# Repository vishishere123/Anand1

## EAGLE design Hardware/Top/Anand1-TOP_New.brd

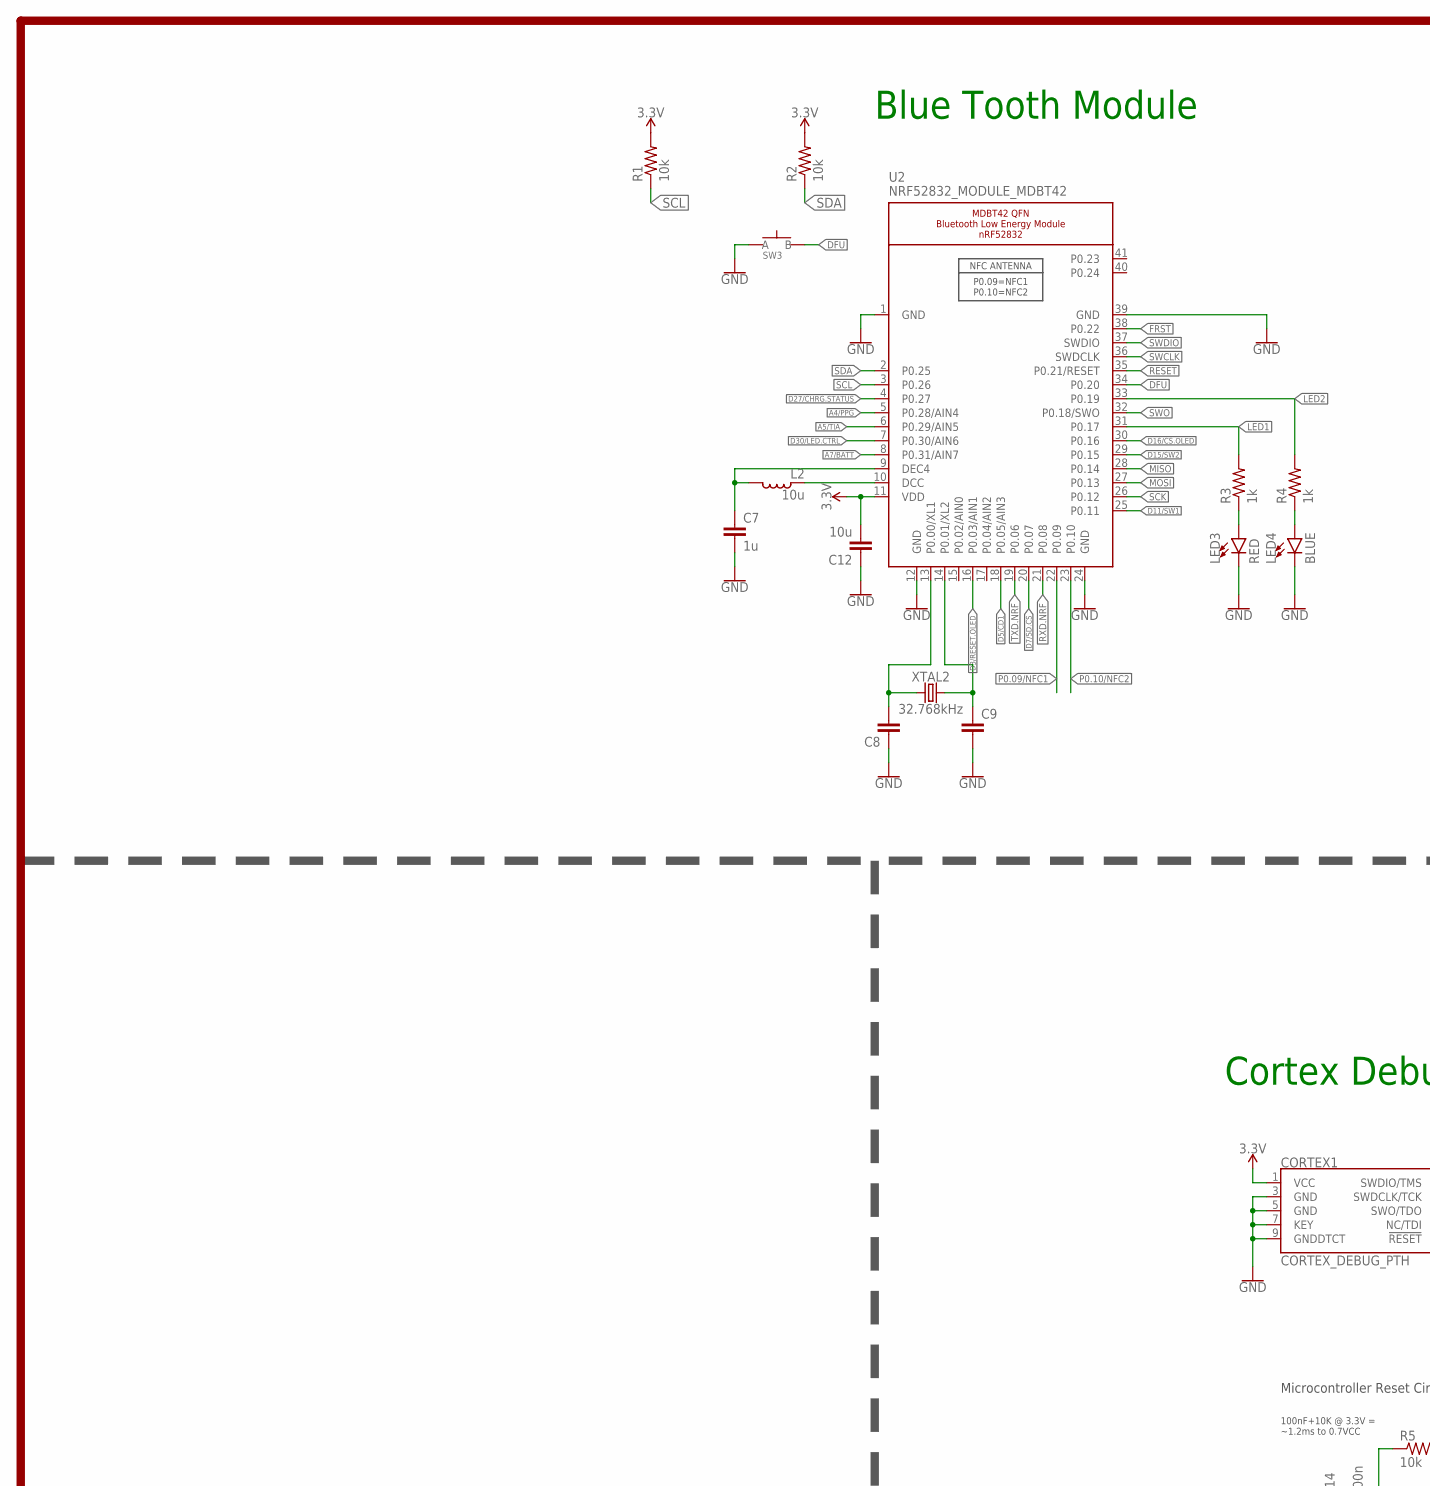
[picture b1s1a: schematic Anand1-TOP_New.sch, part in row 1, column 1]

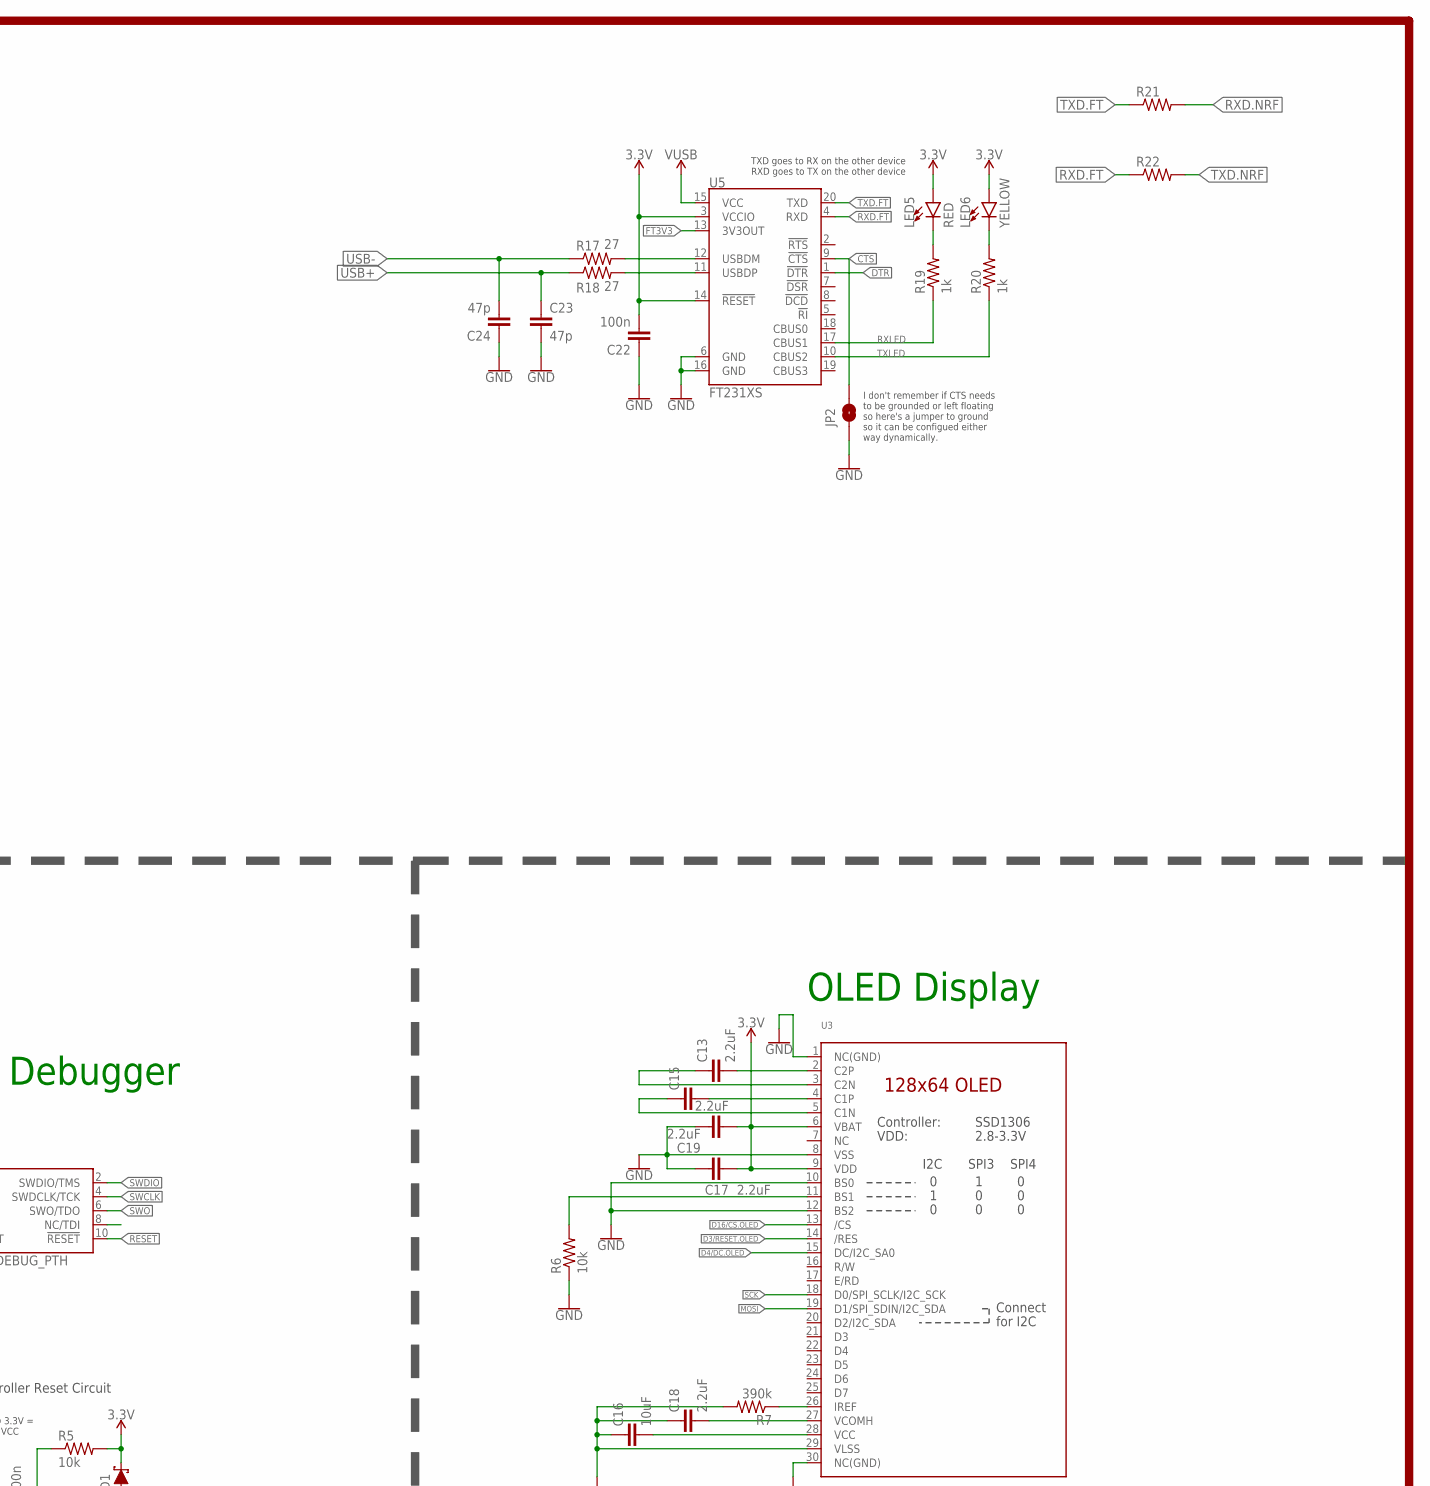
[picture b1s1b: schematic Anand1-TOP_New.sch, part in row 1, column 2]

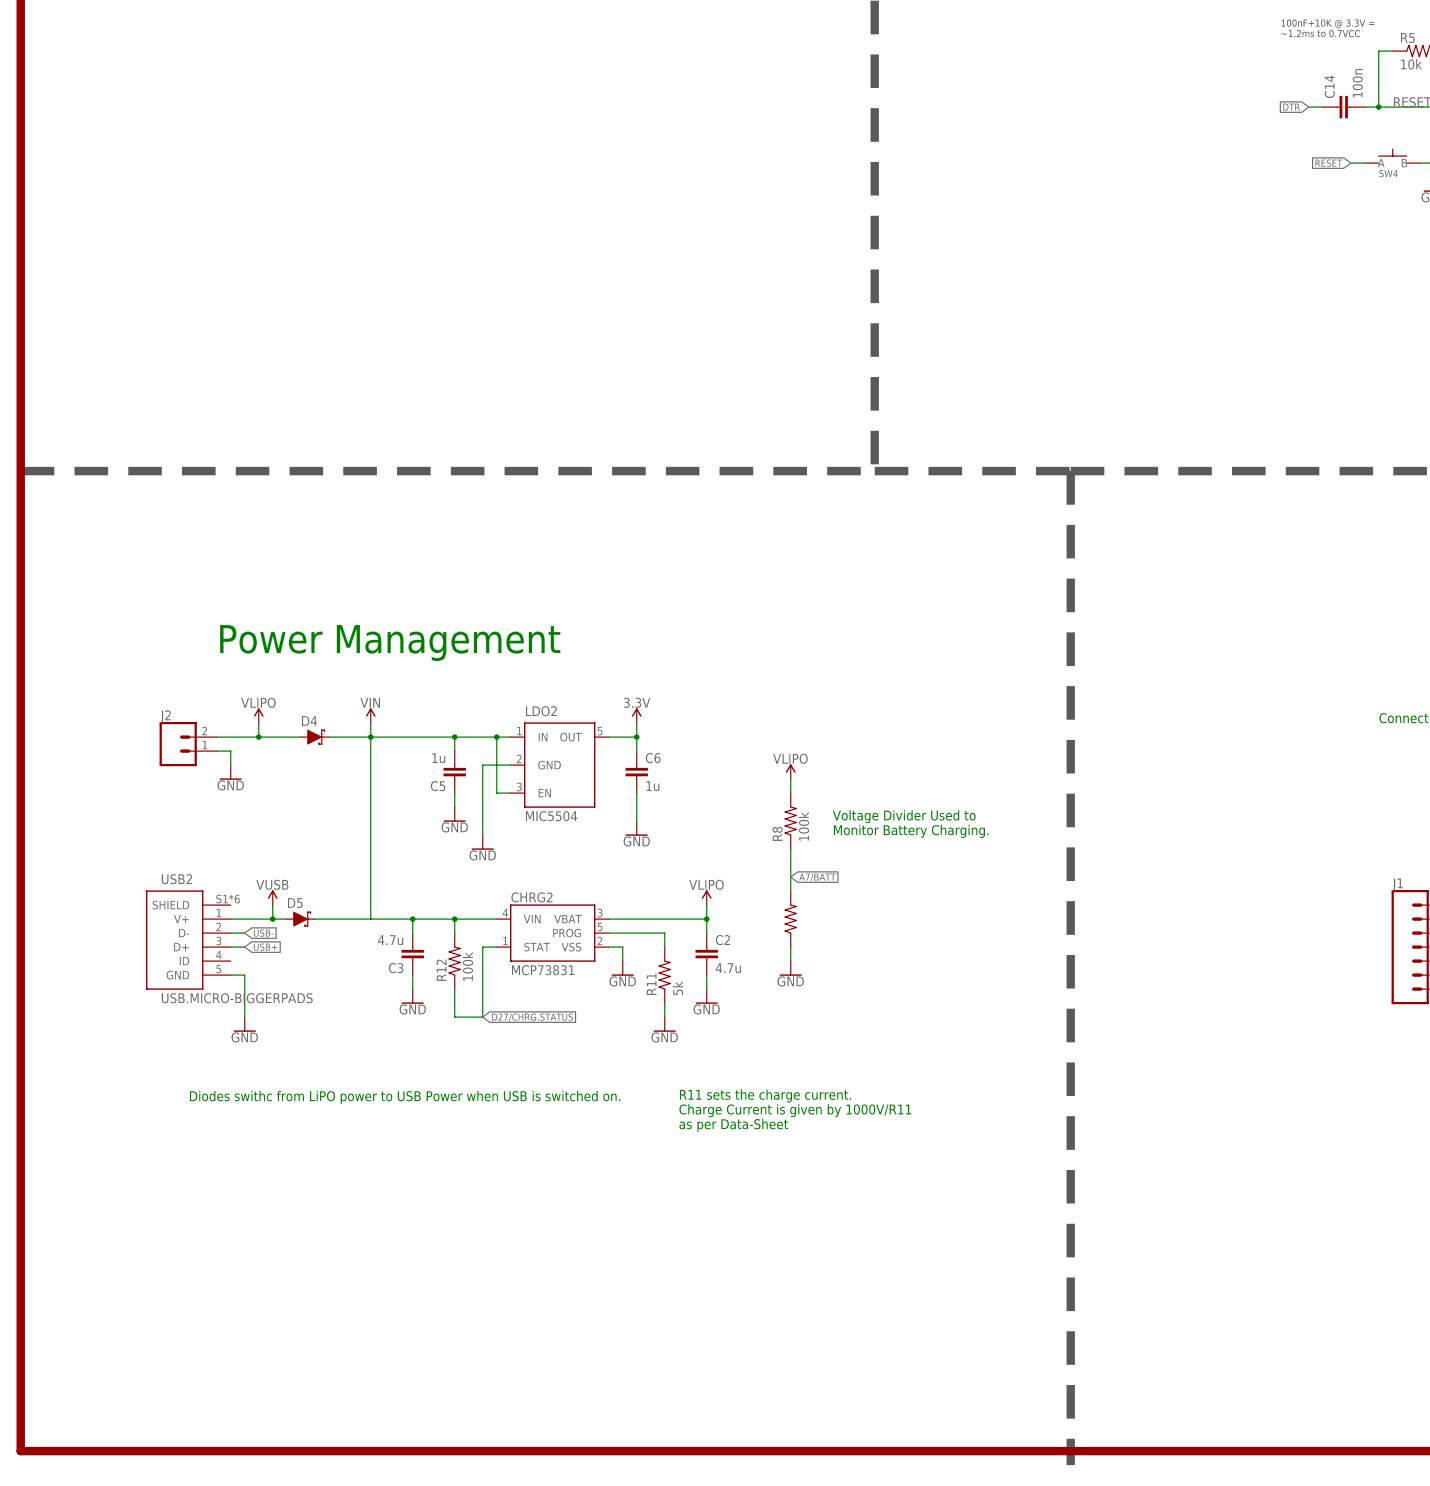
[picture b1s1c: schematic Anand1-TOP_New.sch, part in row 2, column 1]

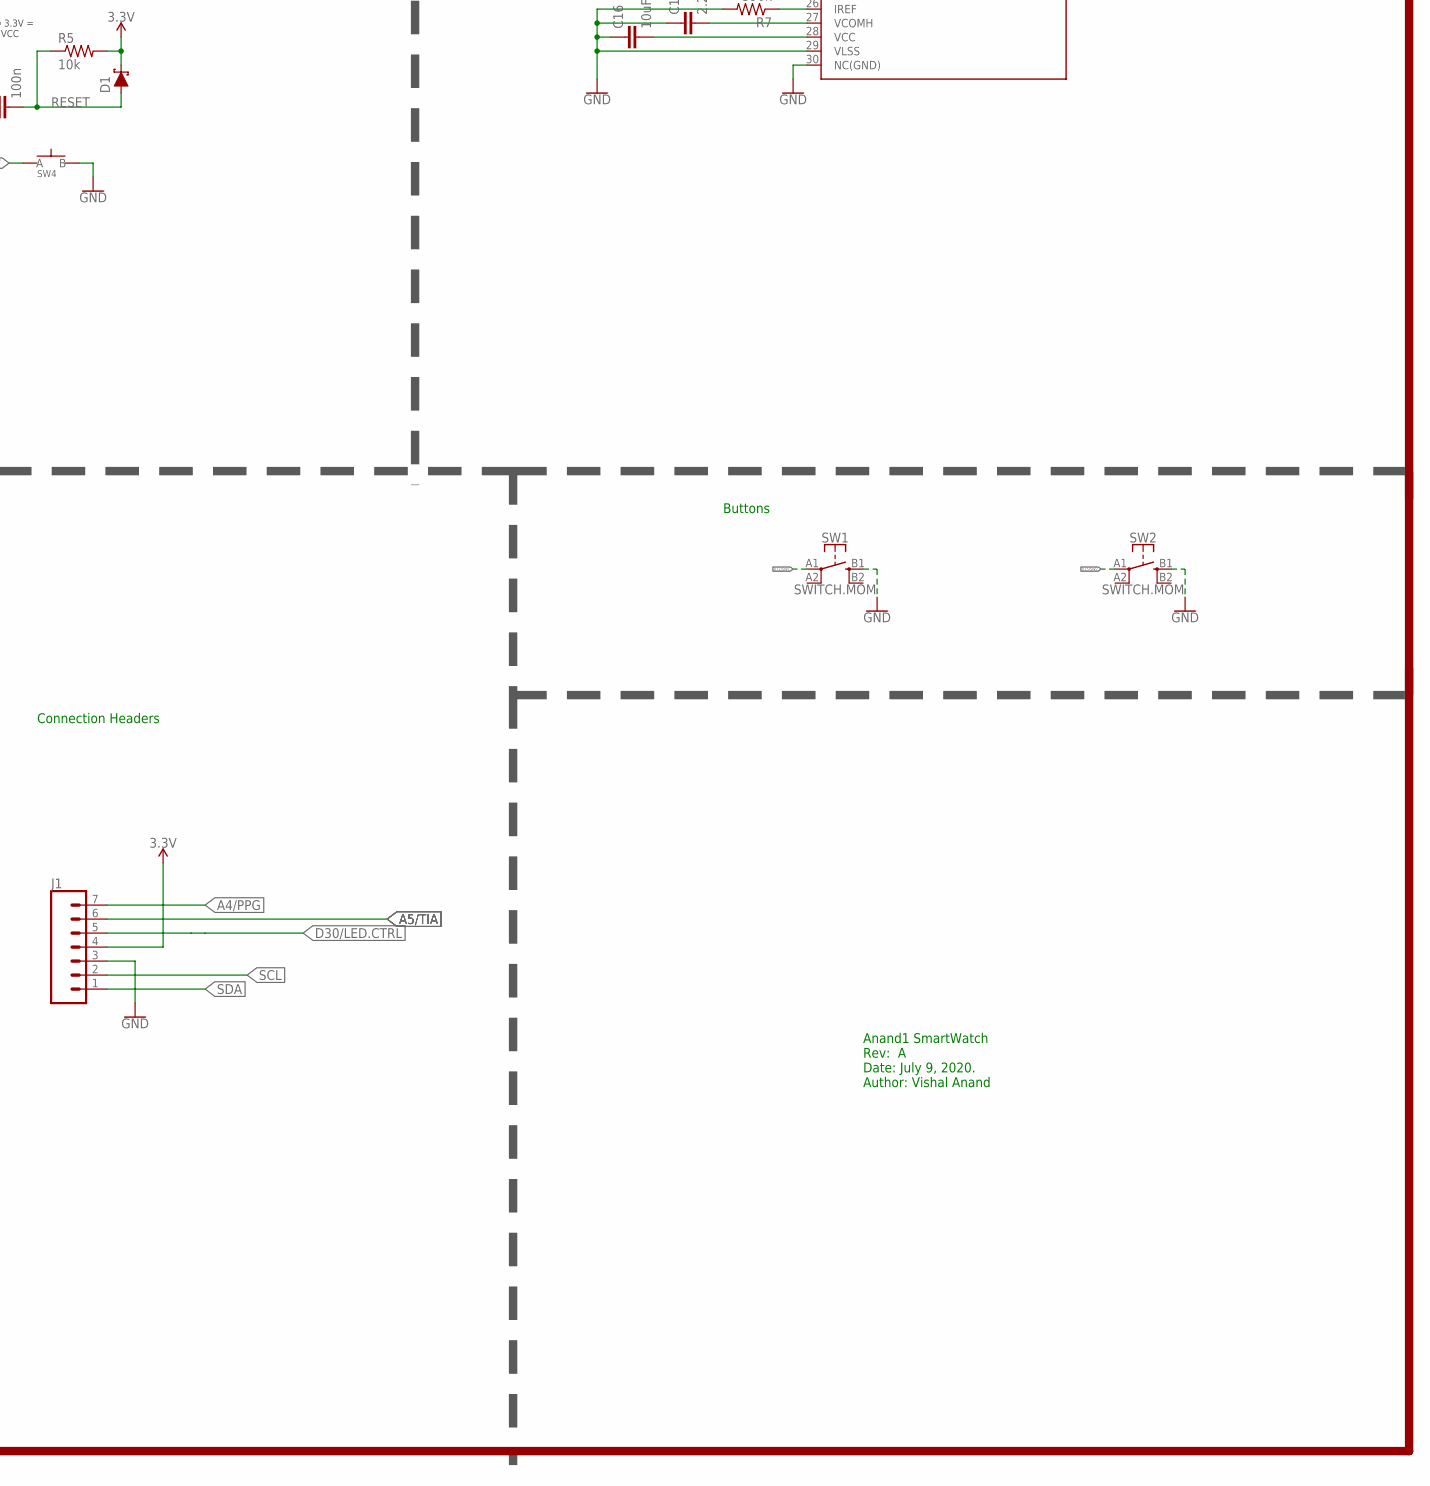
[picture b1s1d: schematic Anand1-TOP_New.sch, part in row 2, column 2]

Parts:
C2, C3: 4.7u; C0603
C5, C6, C7: 1u; C0603
C8, C9: CAPACITOR0603; C0603
C12: 10u; C0805
C13, C15, C17, C18, C19: 2.2uF; C0402
C14, C22: 100n; C0603
C16: 10uF; C0603
C23, C24: 47p; C0603
CHRG2: MCP73831; SOT23-5
CORTEX1: CORTEX_DEBUG_PTH; 2X5-PTH-1.27MM
D1, D4, D5: SCHOTTKY-USC; USC
J1: CONN_07-1.27MM; 1X07_1.27MM
J2: CONN_02; 1X02
JP2: JUMPER-SMT_2_NO_SILK; SMT-JUMPER_2_NO_SILK
L2: 10u; L0603
LDO2: MIC5504; SOT23-5
LED3, LED5: RED; LED-0603
LED4: BLUE; LED-0603
LED6: YELLOW; LED-0603
R1, R2, R5, R6: 10k; R0603
R3, R4, R19, R20: 1k; R0603
R7: 390k; R0603
R8, R9, R12: 100k; R0603
R11: 5k; R0603
R17, R18: 27; R0603
R21, R22: RESISTOR0603; R0603
SW1, SW2: SWITCH.MOM; TACTILE_SWITCH_SMD_6.2MM_TALL
SW3, SW4: SPST-PTS830GG140-COPY.1-3; BUTTON-GULLWING
U2: NRF52832_MODULE_MDBT42; BLE_MODULE_RAYTAC_MDBT42
U3: DISP_OLED_UG-2864HSWEG01-NO-WRAPAROUND; UG-2864HSWEG01_0.96IN_NO-WRAPAROUND
U5: FT231XS; SSOP20_L
USB2: USB.MICRO-BIGGERPADS; USB-MICRO-01.BIGGERPADS
XTAL2: 32.768kHz; 2-SMD.NOLEAD.2.0MMTO1.2MM

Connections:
3.3V: C6.1, C12.2, C17.2, C19.2, C22.2, CORTEX1.1 (VCC), D1.- (C), J1.4, LDO2.5 (OUT), LED5.A, LED6.A, R1.2, R2.2, R5.2, U2.11 (VDD), U3.6 (VBAT), U3.9 (VDD), U5.3 (VCCIO), U5.14 (!RESET)
A4/PPG: J1.7, U2.5 (P0.28/AIN4)
A5/TIA: J1.6, U2.6 (P0.29/AIN5)
A7/BATT: R8.1, R9.2, U2.8 (P0.31/AIN7)
CTS: JP2.2, U5.9 (!CTS)
D3/RESET.OLED: U2.16 (P0.03/AIN1), U3.14 (/RES)
D4/DC.OLED: U3.15 (DC/I2C_SA0)
D5/CD1: U2.18 (P0.05/AIN3)
D7/SD.CS: U2.20 (P0.07)
D11/SW1: SW1.A1 (1), U2.25 (P0.11)
D15/SW2: SW2.A1 (1), U2.29 (P0.15)
D16/CS.OLED: U2.30 (P0.16), U3.13 (/CS)
D27/CHRG.STATUS: CHRG2.1 (STAT), R12.1, U2.4 (P0.27)
D30/LED.CTRL: J1.5, U2.7 (P0.30/AIN6)
DFU: SW3.3 (B), U2.34 (P0.20)
DTR: C14.1, U5.1 (!DTR)
FRST: U2.38 (P0.22)
FT3V3: U5.13 (3V3OUT)
GND: C2.2, C3.1, C5.1, C6.2, C7.2, C8.1, C9.2, C12.1, C16.1, C17.1, C18.1, C19.1, C22.1, C23.2, C24.1, CHRG2.2 (VSS), CORTEX1.3 (GND), CORTEX1.5 (GND), CORTEX1.7 (KEY), CORTEX1.9 (GNDDTCT), J1.3, J2.1, JP2.1, LDO2.2 (GND), LED3.C, LED4.C, R6.1, R7.2, R9.1, R11.1, SW1.B1 (3), SW2.B1 (3), SW3.1 (A), SW4.3 (B), U2.1 (GND), U2.12 (GND), U2.24 (GND), U2.39 (GND), U3.1 (NC(GND)), U3.8 (VSS), U3.10 (BS0), U3.12 (BS2), U3.29 (VLSS), U3.30 (NC(GND)), U5.6 (GND), U5.16 (GND), USB2.5 (GND)
LED1: R3.2, U2.31 (P0.17)
LED2: R4.2, U2.33 (P0.19)
MISO: U2.28 (P0.14)
MOSI: U2.27 (P0.13), U3.19 (D1/SPI_SDIN/I2C_SDA)
unnamed: R6.2, U3.11 (BS1)
unnamed: R7.1, U3.26 (IREF)
unnamed: C13.2, U3.2 (C2P)
unnamed: C8.2, U2.13 (P0.00/XL1), XTAL2.P$1 (1)
unnamed: C13.1, U3.3 (C2N)
unnamed: C9.1, U2.14 (P0.01/XL2), XTAL2.P$2 (2)
unnamed: C15.2, U3.4 (C1P)
unnamed: C15.1, U3.5 (C1N)
unnamed: LED3.A, R3.1
unnamed: LED4.A, R4.1
unnamed: L2.1, U2.10 (DCC)
unnamed: C7.1, L2.2, U2.9 (DEC4)
unnamed: C16.2, U3.28 (VCC)
unnamed: C18.2, U3.27 (VCOMH)
unnamed: CHRG2.5 (PROG), R11.2
unnamed: R17.2, U5.12 (USBDM)
unnamed: R18.2, U5.11 (USBDP)
unnamed: LED5.C, R19.2
unnamed: LED6.C, R20.2
P0.09/NFC1: U2.22 (P0.09)
P0.10/NFC2: U2.23 (P0.10)
RESET: C14.2, CORTEX1.10 (!RESET), D1.+ (A), R5.1, SW4.1 (A), U2.35 (P0.21/RESET)
RXD.FT: R22.1, U5.4 (RXD)
RXD.NRF: R21.2, U2.21 (P0.08)
RXLED: R19.1, U5.17 (CBUS1)
SCK: U2.26 (P0.12), U3.18 (D0/SPI_SCLK/I2C_SCK)
SCL: J1.2, R1.1, U2.3 (P0.26)
SDA: J1.1, R2.1, U2.2 (P0.25)
SWCLK: CORTEX1.4 (SWDCLK/TCK), U2.36 (SWDCLK)
SWDIO: CORTEX1.2 (SWDIO/TMS), U2.37 (SWDIO)
SWO: CORTEX1.6 (SWO/TDO), U2.32 (P0.18/SWO)
TXD.FT: R21.1, U5.20 (TXD)
TXD.NRF: R22.2, U2.19 (P0.06)
TXLED: R20.1, U5.10 (CBUS2)
USB+: C23.1, R18.1, USB2.3 (D+)
USB-: C24.2, R17.1, USB2.2 (D-)
VIN1: C3.2, C5.2, CHRG2.4 (VIN), D4.- (C), D5.- (C), LDO2.1 (IN), LDO2.3 (EN), R12.2
VLIPO: C2.1, CHRG2.3 (VBAT), D4.+ (A), J2.2, R8.2
V_USB: D5.+ (A), U5.15 (VCC), USB2.1 (V+)

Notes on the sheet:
Microcontroller Reset Circuit
100nF+10K @ 3.3V = ~1.2ms to 0.7VCC
OLED Display
Cortex Debugger
Power Management
Blue Tooth Module
TXD goes to RX on the other device RXD goes to TX on the other device
I don't remember if CTS needs to be grounded or left floating so here's a jumper to ground so it can be configued either way dynamically.
Diodes swithc from LiPO power to USB Power when USB is switched on.
Anand1 SmartWatch Rev: A Date: July 9, 2020. Author: Vishal Anand
R11 sets the charge current. Charge Current is given by 1000V/R11 as per Data-Sheet
Voltage Divider Used to Monitor Battery Charging.
Connection Headers
Buttons

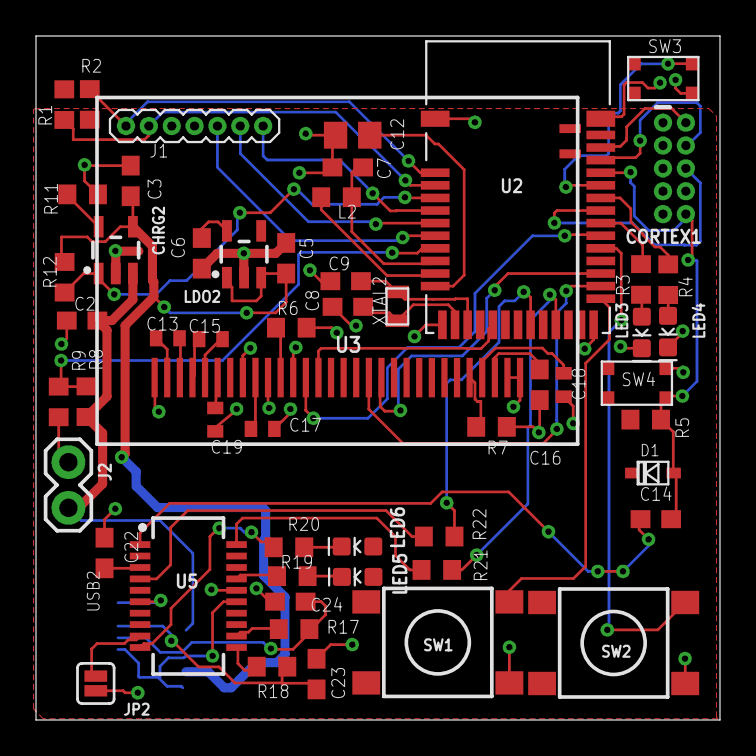
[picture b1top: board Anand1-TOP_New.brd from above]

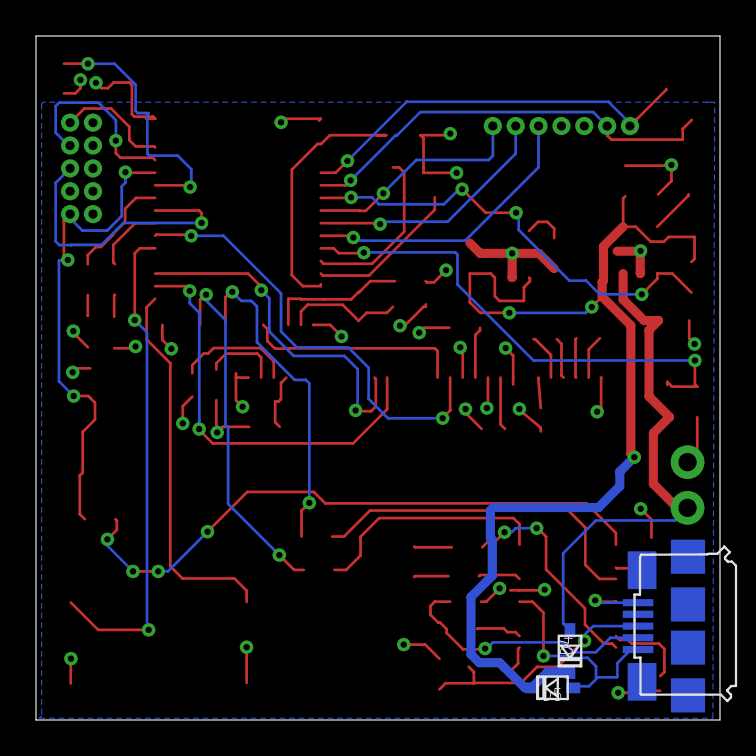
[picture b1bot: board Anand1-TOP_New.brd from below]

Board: 2 copper layers, 38.0 x 38.0 mm, 58 parts (3 on the bottom side), 54 nets.

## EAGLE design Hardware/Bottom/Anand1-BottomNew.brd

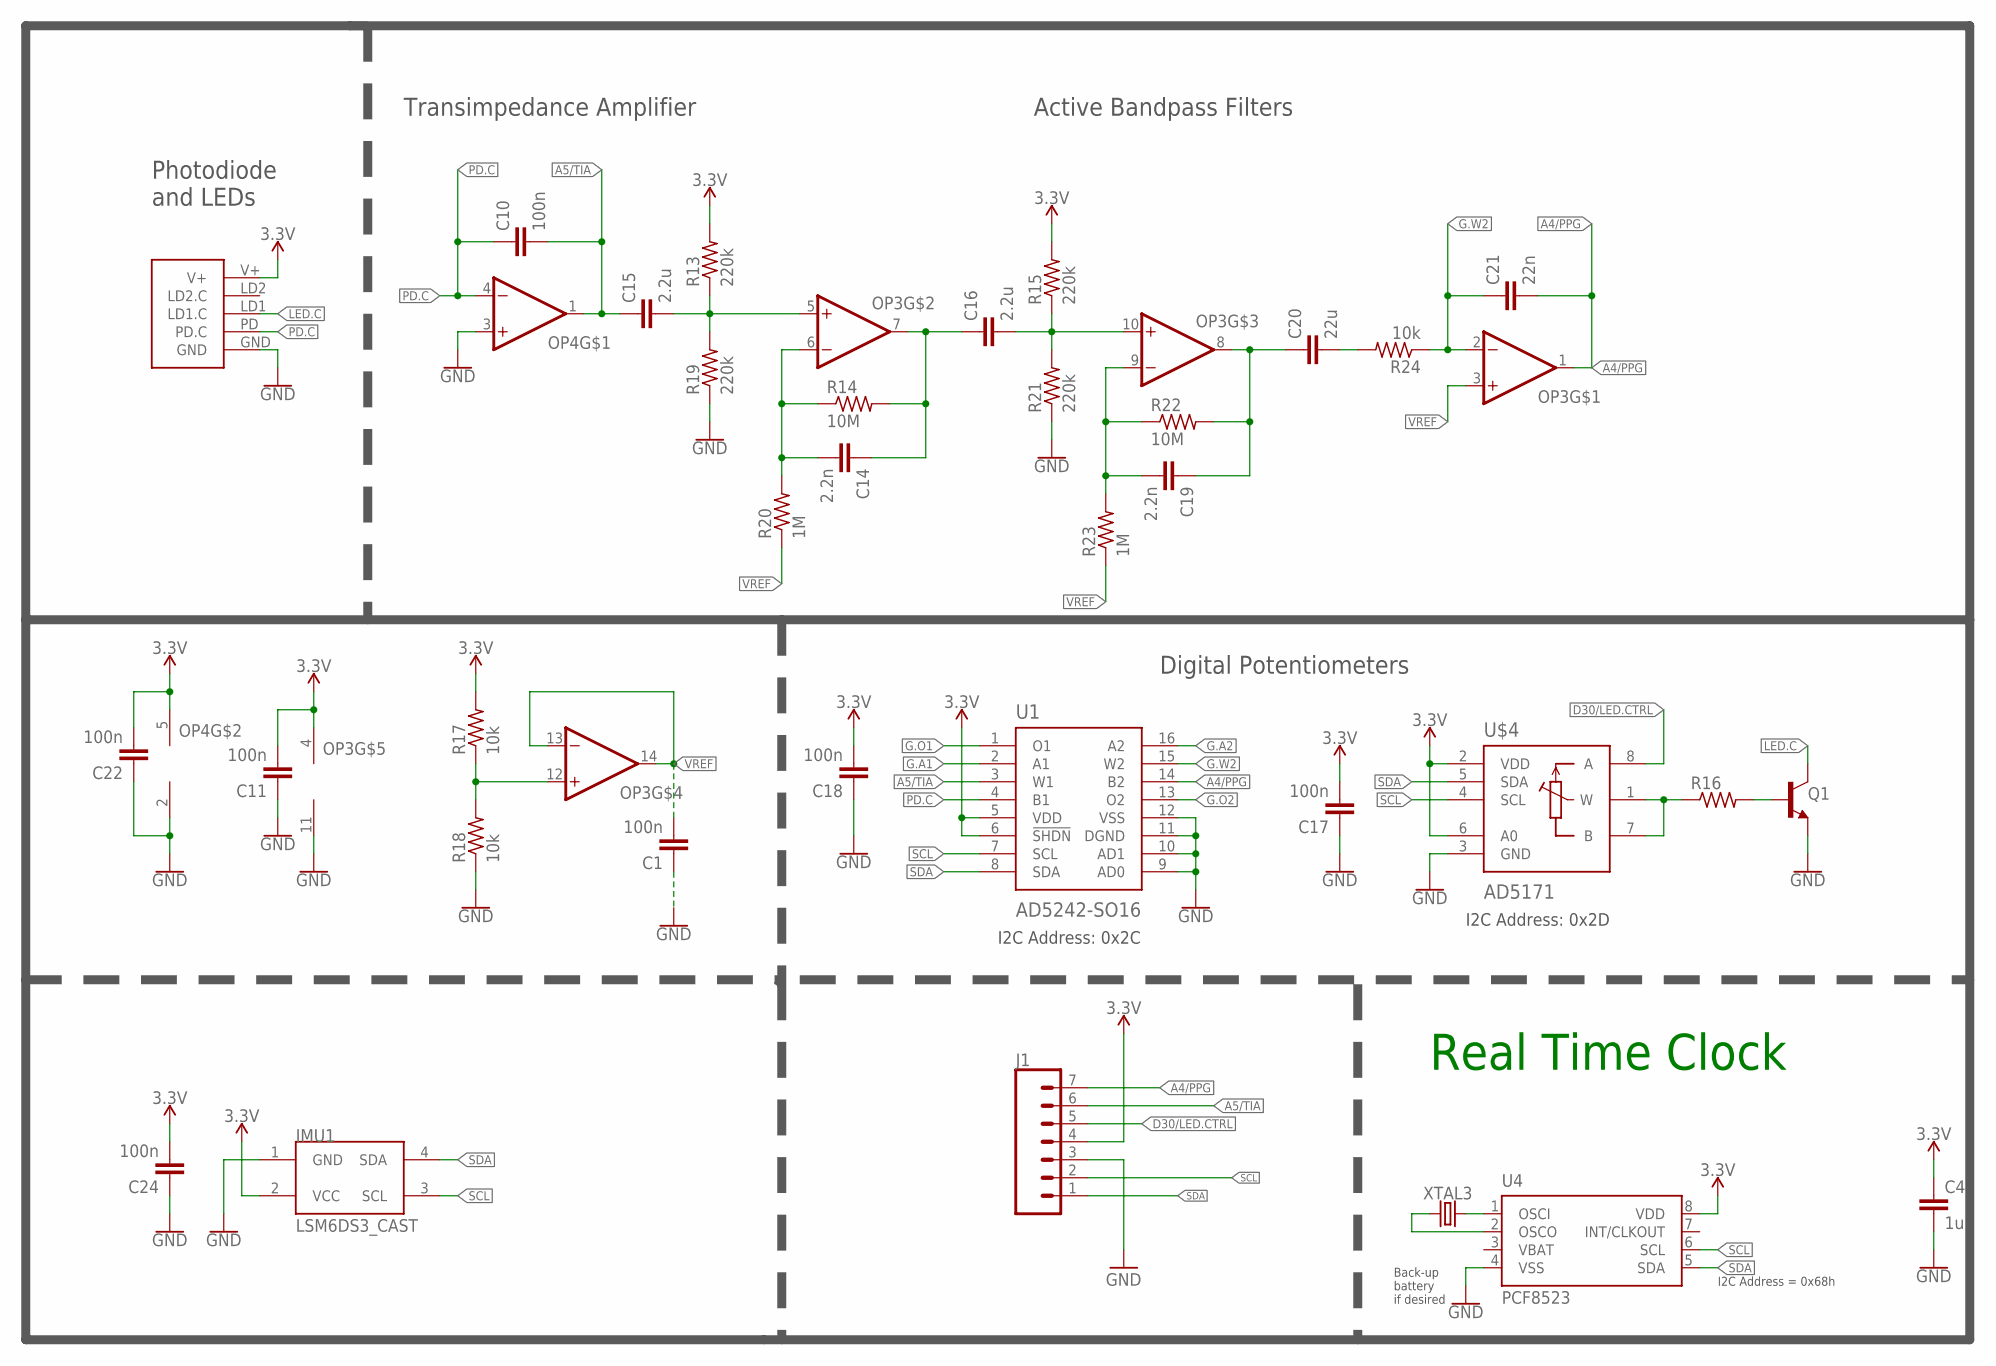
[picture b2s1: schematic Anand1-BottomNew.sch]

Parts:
C1, C10, C11, C17, C18, C22, C24: 100n; C0603
C4: 1u; C0603
C14, C19: 2.2n; C0603
C15, C16: 2.2u; C0603
C20: 22u; C0603
C21: 22n; C0603
IMU1: LSM6DS3_CAST
J1: CONN_07-1.27MM; 1X07_1.27MM
OP3: OP-QUAD-SO14; SO14
OP4: OP-SINGLEOT; SOT23-5
Q1: NPN-GENERIC; SOT23-3
R13, R15, R19, R21: 220k; R0603
R14, R22: 10M; R0603
R16: RESISTOR0603; R0603
R17, R18: 10k; R0402
R20, R23: 1M; R0603
R24: 10k; R0603
U1: AD5242-SO16; SO16
U4: PCF8523; SO8; DIGIKEY 568-5306-1-ND
U$3: PPG.MODULE.2
U$4: AD5171; SOT-23-8
XTAL3: 32.7680kHz; 2-SMD.NOLEAD.2.0MMTO1.2MM

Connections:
3.3V: C4.1, C11.2, C17.2, C18.2, C22.2, C24.2, IMU1.2 (VCC), J1.4, OP3.4 (V+), OP4.5 (V+), R13.2, R15.2, R17.2, U1.5 (VDD), U1.6 (!SHDN), U4.8 (VDD), U$3.V+, U$4.2 (VDD), U$4.6 (A0)
A4/PPG: C21.2, J1.7, OP3.1 (OUT), U1.14 (B2)
A5/TIA: C10.2, C15.1, J1.6, OP4.1 (OUT), U1.3 (W1)
D30/LED.CTRL: J1.5, U$4.8 (A)
G.A1: U1.2 (A1)
G.A2: U1.16 (A2)
G.O1: U1.1 (O1)
G.O2: U1.13 (O2)
G.W2: C21.1, OP3.2 (-IN), R24.1, U1.15 (W2)
GND: C1.1, C4.2, C11.1, C17.1, C18.1, C22.1, C24.1, IMU1.1 (GND), J1.3, OP3.11 (V-), OP4.2 (V-), OP4.3 (+IN), Q1.2 (E), R18.1, R19.1, R21.1, U1.9 (AD0), U1.10 (AD1), U1.11 (DGND), U1.12 (VSS), U4.4 (VSS), U$3.GND, U$4.3 (GND)
LED.C: Q1.3 (C), U$3.LD1 (LD1.C)
unnamed: U4.2 (OSCO), XTAL3.P$1 (1)
unnamed: U4.1 (OSCI), XTAL3.P$2 (2)
unnamed: Q1.1 (B), R16.2
unnamed: R16.1, U$4.1 (W), U$4.7 (B)
unnamed: OP3.12 (+IN), R17.1, R18.2
unnamed: C15.2, OP3.5 (+IN), R13.1, R19.2
unnamed: C14.2, OP3.6 (-IN), R14.1, R20.2
unnamed: C14.1, C16.1, OP3.7 (OUT), R14.2
unnamed: C16.2, OP3.10 (+IN), R15.1, R21.2
unnamed: C19.2, OP3.9 (-IN), R22.1, R23.2
unnamed: C19.1, C20.1, OP3.8 (OUT), R22.2
unnamed: C20.2, R24.2
PD.C: C10.1, OP4.4 (-IN), U1.4 (B1), U$3.PD (PD.C)
SCL: IMU1.3 (SCL), J1.2, U1.7 (SCL), U4.6 (SCL), U$4.4 (SCL)
SDA: IMU1.4 (SDA), J1.1, U1.8 (SDA), U4.5 (SDA), U$4.5 (SDA)
VBAT: U4.3 (VBAT)
VREF: C1.2, OP3.3 (+IN), OP3.13 (-IN), OP3.14 (OUT), R20.1, R23.1

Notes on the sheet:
Photodiode and LEDs
Active Bandpass Filters
Digital Potentiometers
Transimpedance Amplifier
I2C Address: 0x2C
I2C Address: 0x2D
I2C Address = 0x68h
Back-up battery if desired
Real Time Clock

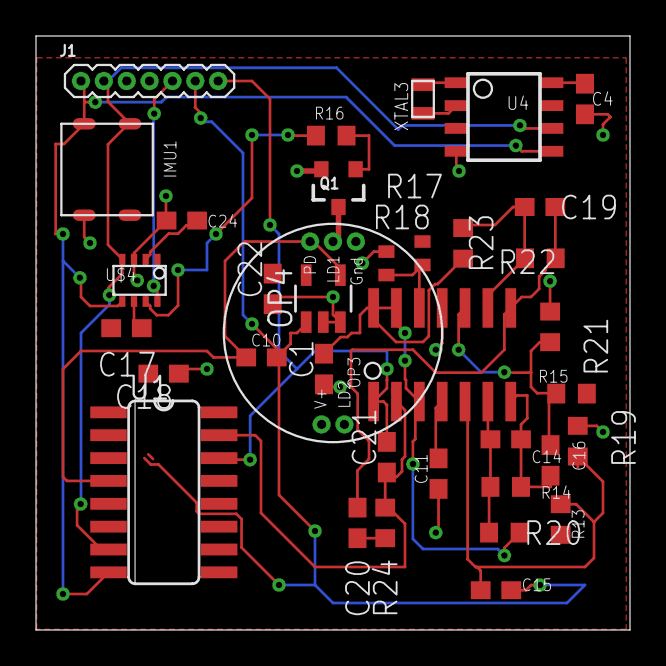
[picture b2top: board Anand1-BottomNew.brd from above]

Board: 2 copper layers, 33.0 x 33.0 mm, 36 parts (0 on the bottom side), 23 nets.

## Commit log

2020-05-28 features_List
2020-06-04 Eagle Files for Top module
2020-06-04 Eagle Files for Bottom Module
2020-06-04 EAGLE Files for PPG Module
2020-06-04 Arduino File for Software
2020-06-04 Top board not routed yet
2020-07-09 added new top and bottom board and schematic files
2020-11-22 added PPG Module board, BOM, and gitignore

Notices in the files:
parts and their libraries:
SparkFun-PowerSymbols: Licensing: Creative Commons ShareAlike 4.0 International - https://creativecommons.org/licenses/by-sa/4.0
